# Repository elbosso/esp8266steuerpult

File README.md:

# esp8266steuerpult

<!---

--->

This repository contains software fur re-purposing a vintage control 
unit with numerous analogue and digital inputs and some digital outputs (LEDs).

The Idea was to collect the data from the outputs and to send them via 
MQTT to a broker where subscribers can use them (https://smarthome-blogger.de/tutorial/esp8266-mqtt-tutorial/).

For gathering the analogue data, we will use a ADS1x15 (http://www.esp8266learning.com/ads1115-analog-to-digital-converter-and-esp8266.php)

The data for connecting with your wifi is located in a header file named `wifi_security.h` that i did
not commit for obvious reasons. Its contents look something like the contents of the example named
`wifi_security_h.example`:

```
#ifndef WIFISECURITY_H
#define WIFISECURITY_H

char wifi_ssid[]="<wifi_ssid>";
char wifi_pwd[]="<wifi_pwd>";
char wifi_ssid_cell_ap[]="<wifi_ssid_cell_ap>";
char wifi_pwd_cell_ap[]="<wifi_pwd_cell_ap>";

#endif /* WIFISECURITY_H */
```

The define `AT_HOME` is used to control what NTP-server should be used: The source code presumes a local NTP-server 
exists at IP-address `192.168.10.2` if
`AT_HOME` is set to 1 - if this is not so, it currently asks `2.de.pool.ntp.org` for the time.

The define `AT_HOME` also decides which pair of WIFI credentials are to be used.

Instructions for setting up the arduino IDE to actually be able to transfer the code to a Wemos D1 (clone) can be found [here](https://averagemaker.com/2018/03/wemos-d1-mini-setup.html)

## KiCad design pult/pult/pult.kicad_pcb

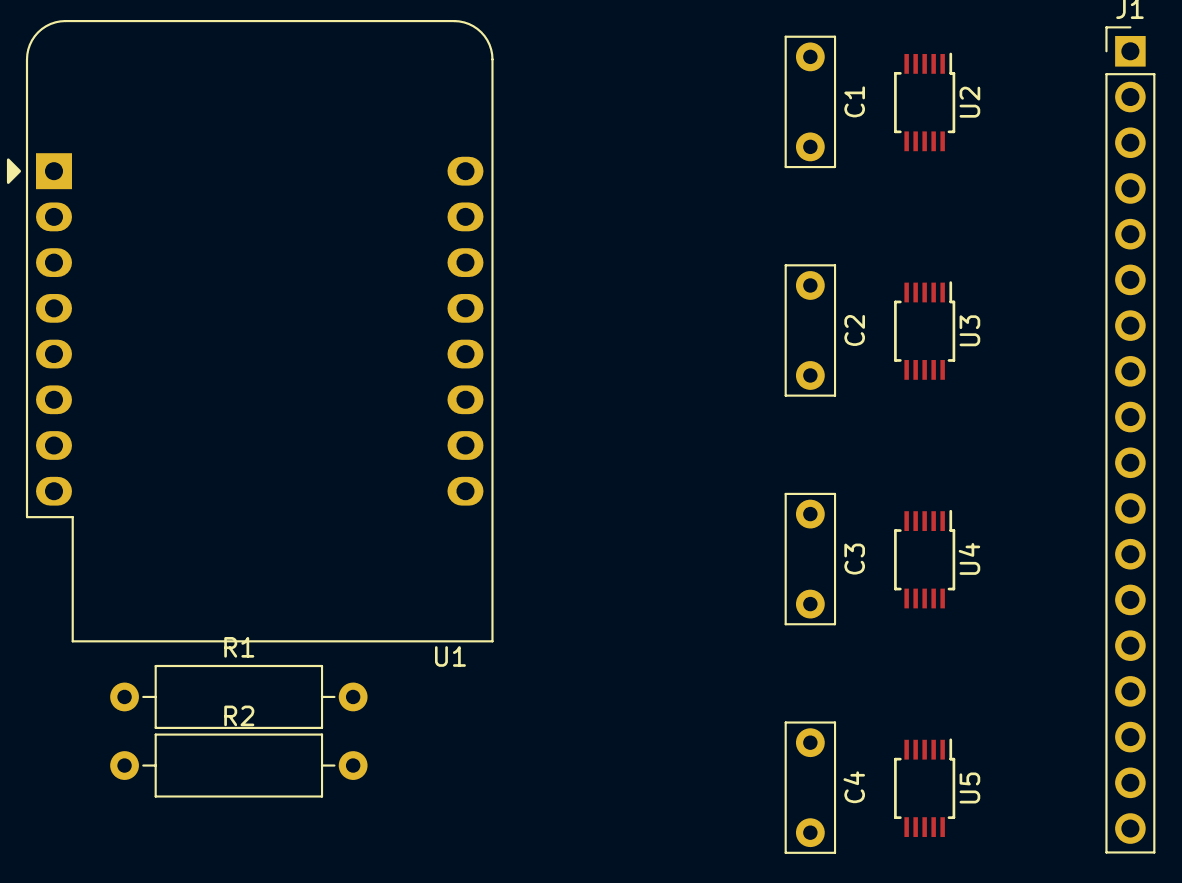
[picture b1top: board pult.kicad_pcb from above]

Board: 2 copper layers, 12 parts (0 on the bottom side), 20 nets, no tracks yet.

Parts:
C1, C2, C3, C4: 100n; C_Rect_L7.0mm_W2.5mm_P5.00mm
J1: Conn_01x18_Male; PinHeader_1x18_P2.54mm_Vertical
R1, R2: 10K; R_Axial_DIN0309_L9.0mm_D3.2mm_P12.70mm_Horizontal
U1: WeMos_D1_mini; WEMOS_D1_mini_light
U2, U3, U4, U5: ADS1015IDGS; TSSOP-10_3x3mm_P0.5mm

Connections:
+5V: C1.2, C2.2, C3.2, C4.2, J1.1, R1.1, R2.1, U1.9, U2.8, U3.1, U3.8, U4.8, U5.8
GND: C1.1, C2.1, C3.1, C4.1, J1.18, U1.10, U2.1, U2.3, U3.3, U4.3, U5.3
Mes01: J1.2, U2.4
Mes02: J1.3, U2.5
Mes03: J1.4, U2.6
Mes04: J1.5, U2.7
Mes11: J1.6, U3.4
Mes12: J1.7, U3.5
Mes13: J1.8, U3.6
Mes14: J1.9, U3.7
Mes21: J1.10, U4.4
Mes22: J1.11, U4.5
Mes23: J1.12, U4.6
Mes24: J1.13, U4.7
Mes31: J1.14, U5.4
Mes32: J1.15, U5.5
Mes33: J1.16, U5.6
Mes34: J1.17, U5.7
SCL: R1.2, U1.14, U2.10, U3.10, U4.10, U5.1, U5.10
SDA: R2.2, U1.13, U2.9, U3.9, U4.1, U4.9, U5.9

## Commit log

2020-03-08 initial hw release
